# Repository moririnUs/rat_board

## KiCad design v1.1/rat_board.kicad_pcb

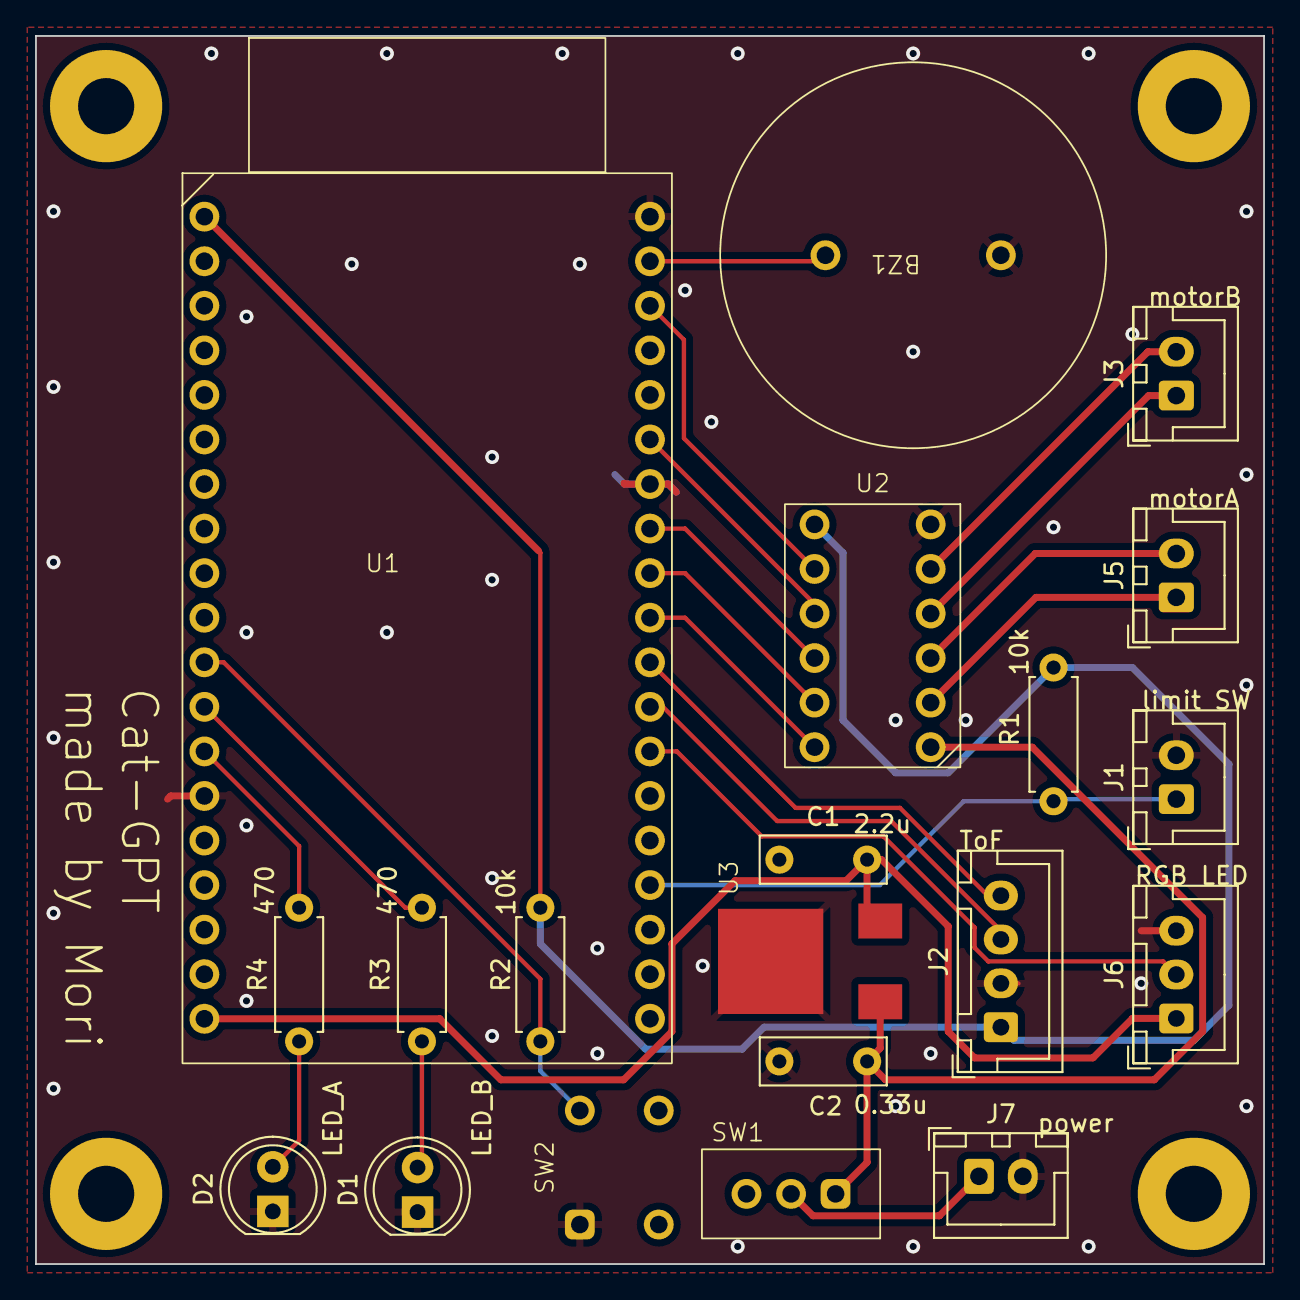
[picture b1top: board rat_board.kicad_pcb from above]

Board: 2 copper layers, 70.0 x 70.0 mm, 24 parts (0 on the bottom side), 24 nets.

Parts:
BZ1: Buzzer; PKM22EPP-40
C1: 2.2u; C_Disc_D7.0mm_W2.5mm_P5.00mm
C2: 0.33u; C_Disc_D7.0mm_W2.5mm_P5.00mm
D1: LED BLUE; LED_D5.0mm
D2: LED WHITE; LED_D5.0mm
H1, H2, H3, H4: MountingHole_Pad; MountingHole_3.2mm_M3_Pad
J1, J3, J5, J7: Conn_01x02; JST_XH_B2B-XH-A_1x02_P2.50mm_Vertical
J2: Conn_01x04; JST_XH_B4B-XH-A_1x04_P2.50mm_Vertical
J6: Conn_01x03; JST_XH_B3B-XH-A_1x03_P2.50mm_Vertical
R1, R2: 10k; R_Axial_DIN0207_L6.3mm_D2.5mm_P7.62mm_Horizontal
R3, R4: 470; R_Axial_DIN0207_L6.3mm_D2.5mm_P7.62mm_Horizontal
SW1: SW_SPDT; switch
SW2: SW_Push; tact_switch
U1: ESP32
U2: DRV8835
U3: NJM2845DL-05; NJM2845

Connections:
+3.3V: J2.1, R1.1, R2.1, U1.1 (3V3), U2.7 (Vcc)
+5V: C1.1, J6.1, U1.19 (5V), U3.3 (OUT)
AIN1: U1.33 (IO21), U2.9 (AIN1)
AIN2: U1.31 (IO19), U2.10 (AIN2)
BIN1: U1.30 (IO18), U2.11 (BIN1)
BIN2: U1.29 (IO5), U2.12 (BIN2)
BUZZER: BZ1.1 (-), U1.37 (IO23)
GND: BZ1.2 (+), C1.2, C2.1, D1.1 (K), D2.1 (K), J1.2, J2.2, J6.3, J7.2, SW2.1, U1.14 (GND), U1.32 (GND), U1.38 (GND), U2.6 (GND), U3.2 (GND)
LED_A: R3.2, U1.12 (IO14)
LED_B: R4.2, U1.13 (IO12)
LIMIT_SW: J1.1, R1.2, U1.23 (IO15)
MODE: U1.36 (IO22), U2.8 (MODE)
unnamed: D1.2 (A), R3.1
unnamed: D2.2 (A), R4.1
unnamed: J3.1, U2.4 (BOUT1)
unnamed: J3.2, U2.5 (BOUT2)
unnamed: J5.1, U2.2 (AOUT1)
unnamed: J5.2, U2.3 (AOUT2)
unnamed: J7.1, SW1.2 (B)
RGBLED: J6.2, U1.26 (IO4)
SCL: J2.4, U1.28 (IO17)
SDA: J2.3, U1.27 (IO16)
SW: R2.2, SW2.2, U1.11 (IO27)
VCC: C2.2, SW1.1 (A), U2.1 (VM), U3.1 (IN)

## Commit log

2023-11-13 init
2023-11-27 refactor: ディレクトリ構成を変更、回路図を見やすくした
2023-11-27 feat: 基板できた！
2023-11-28 clean: コネクタに接続機器名、素子に規格を記述
2023-12-07 feat: gerberファイルを追加
2023-12-07 fix: ガーバーデータのドリルデータがおかしかったので修正
